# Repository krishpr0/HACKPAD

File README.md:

# The Weird MACROPAD

- A 4x4 Key MacroPad,

- So What's this,

This is a Large macropad, I wanted to develop this for the unusal uses such as while gaming, editing, and production of the 3d models shorcuts. 

This operates on the Seeed Studio Xiao RP2040 DIP module with the QMK firmware.

## Hardware:- 

- MCU: Seeed XIAO RP2040 DIP
- Switches: 16x Cherry MX compatible Switches
- LED: 16x SK6812 RBG LED

# Programming,
- Its running the default firmware (QMK firmware) but you can update it to the system you want.

# BOM,

- 16x Cherry MX Switches, 16x SK6812 MINI LEDs, 1x XIAO RP2040, 16x Blank DSA Keycaps,  4x M3x16 Bolts,  4x M3 Heatset Inserts ~100g PLA

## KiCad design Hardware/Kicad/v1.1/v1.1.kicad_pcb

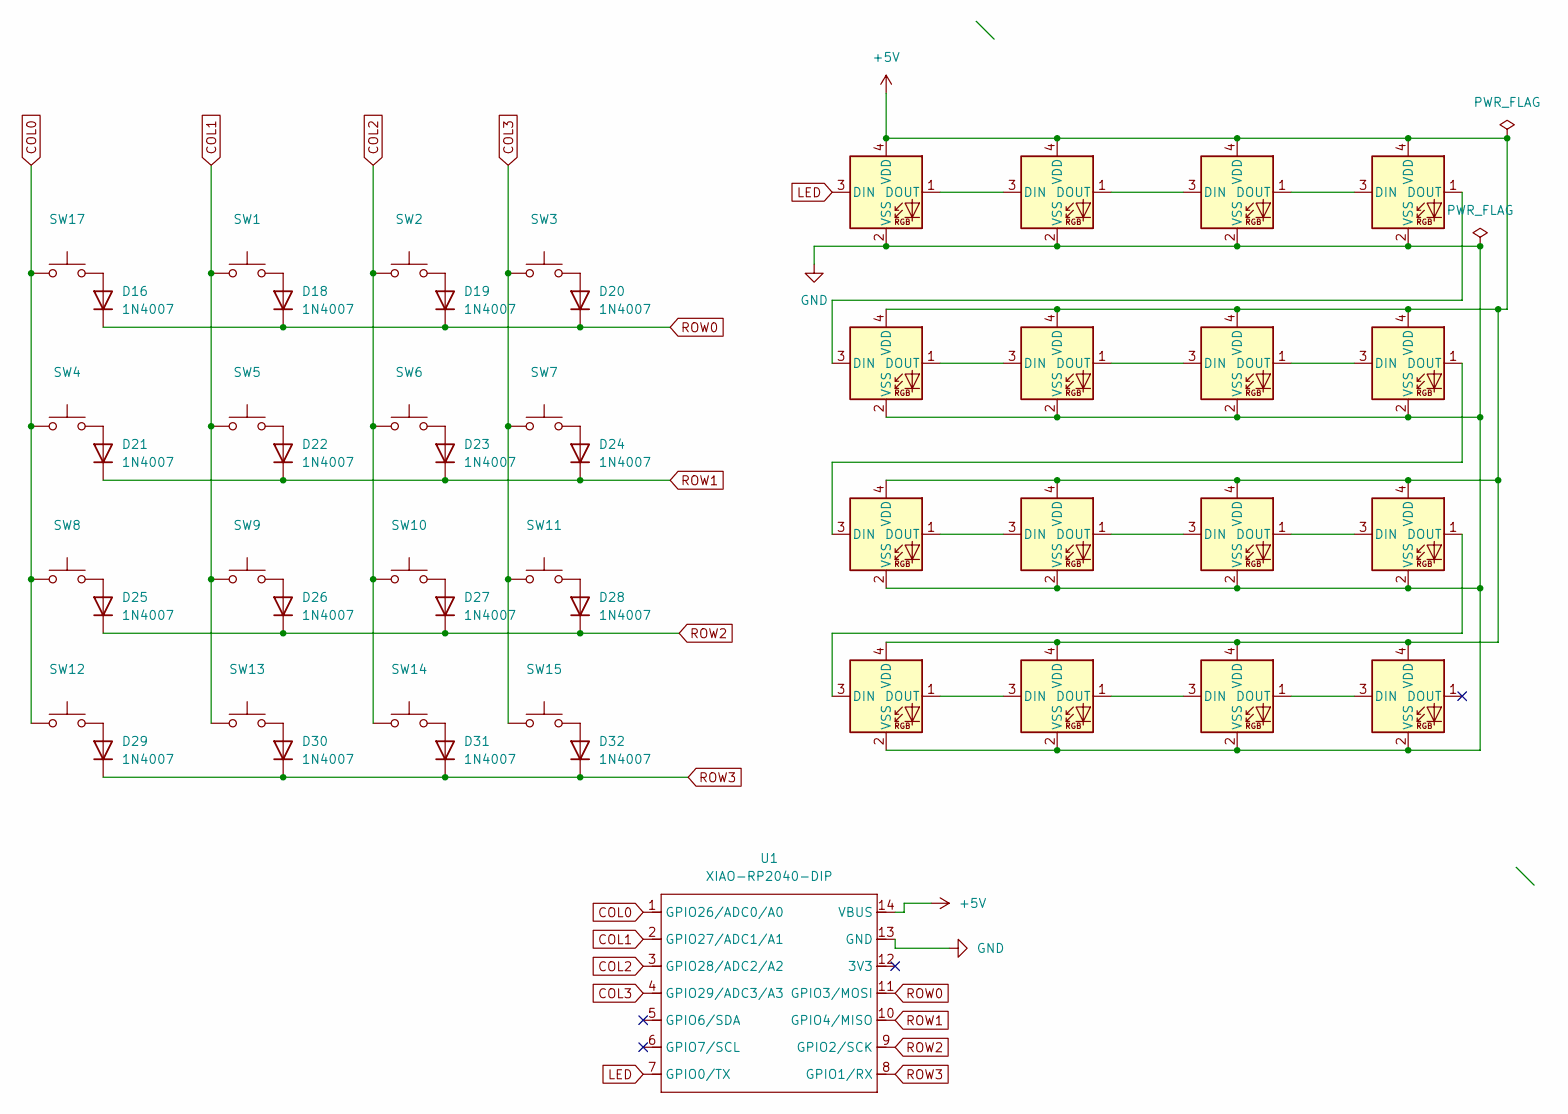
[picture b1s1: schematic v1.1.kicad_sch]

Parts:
D1, D2, D3, D4, D5, D6, D7, D8, D9, D10, D11, D12, D13, D14, D15, D17: SK6812MINI; LED_SK6812MINI_PLCC4_3.5x3.5mm_P1.75mm
D16, D18, D19, D20, D21, D22, D23, D24, D25, D26, D27, D28, D29, D30, D31, D32: 1N4007; D_DO-41_SOD81_P10.16mm_Horizontal
SW1, SW2, SW3, SW4, SW5, SW6, SW7, SW8, SW9, SW10, SW11, SW12, SW13, SW14, SW15, SW17: SW_Push; SW_Cherry_MX_1.00u_PCB
U1: XIAO-RP2040-DIP; XIAO-RP2040-SMD

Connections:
+5V: D1.4 (VDD), D2.4 (VDD), D3.4 (VDD), D4.4 (VDD), D5.4 (VDD), D6.4 (VDD), D7.4 (VDD), D8.4 (VDD), D9.4 (VDD), D10.4 (VDD), D11.4 (VDD), D12.4 (VDD), D13.4 (VDD), D14.4 (VDD), D15.4 (VDD), D17.4 (VDD), U1.14 (VBUS)
COL0: SW4.1, SW8.1, SW12.1, SW17.1, U1.1 (GPIO26/ADC0/A0)
COL1: SW1.1, SW5.1, SW9.1, SW13.1, U1.2 (GPIO27/ADC1/A1)
COL2: SW2.1, SW6.1, SW10.1, SW14.1, U1.3 (GPIO28/ADC2/A2)
COL3: SW3.1, SW7.1, SW11.1, SW15.1, U1.4 (GPIO29/ADC3/A3)
GND: D1.2 (VSS), D2.2 (VSS), D3.2 (VSS), D4.2 (VSS), D5.2 (VSS), D6.2 (VSS), D7.2 (VSS), D8.2 (VSS), D9.2 (VSS), D10.2 (VSS), D11.2 (VSS), D12.2 (VSS), D13.2 (VSS), D14.2 (VSS), D15.2 (VSS), D17.2 (VSS), U1.13 (GND)
LED: D17.3 (DIN), U1.7 (GPIO0/TX)
unnamed: D1.3 (DIN), D17.1 (DOUT)
unnamed: D1.1 (DOUT), D2.3 (DIN)
unnamed: D2.1 (DOUT), D3.3 (DIN)
unnamed: D3.1 (DOUT), D4.3 (DIN)
unnamed: D4.1 (DOUT), D5.3 (DIN)
unnamed: D5.1 (DOUT), D6.3 (DIN)
unnamed: D6.1 (DOUT), D7.3 (DIN)
unnamed: D7.1 (DOUT), D8.3 (DIN)
unnamed: D8.1 (DOUT), D9.3 (DIN)
unnamed: D9.1 (DOUT), D10.3 (DIN)
unnamed: D10.1 (DOUT), D11.3 (DIN)
unnamed: D11.1 (DOUT), D12.3 (DIN)
unnamed: D12.1 (DOUT), D13.3 (DIN)
unnamed: D13.1 (DOUT), D14.3 (DIN)
unnamed: D14.1 (DOUT), D15.3 (DIN)
unnamed: D16.2 (A), SW17.2
unnamed: D18.2 (A), SW1.2
unnamed: D19.2 (A), SW2.2
unnamed: D20.2 (A), SW3.2
unnamed: D21.2 (A), SW4.2
unnamed: D22.2 (A), SW5.2
unnamed: D23.2 (A), SW6.2
unnamed: D24.2 (A), SW7.2
unnamed: D25.2 (A), SW8.2
unnamed: D26.2 (A), SW9.2
unnamed: D27.2 (A), SW10.2
unnamed: D28.2 (A), SW11.2
unnamed: D29.2 (A), SW12.2
unnamed: D30.2 (A), SW13.2
unnamed: D31.2 (A), SW14.2
unnamed: D32.2 (A), SW15.2
ROW0: D16.1 (K), D18.1 (K), D19.1 (K), D20.1 (K), U1.11 (GPIO3/MOSI)
ROW1: D21.1 (K), D22.1 (K), D23.1 (K), D24.1 (K), U1.10 (GPIO4/MISO)
ROW2: D25.1 (K), D26.1 (K), D27.1 (K), D28.1 (K), U1.9 (GPIO2/SCK)
ROW3: D29.1 (K), D30.1 (K), D31.1 (K), D32.1 (K), U1.8 (GPIO1/RX)

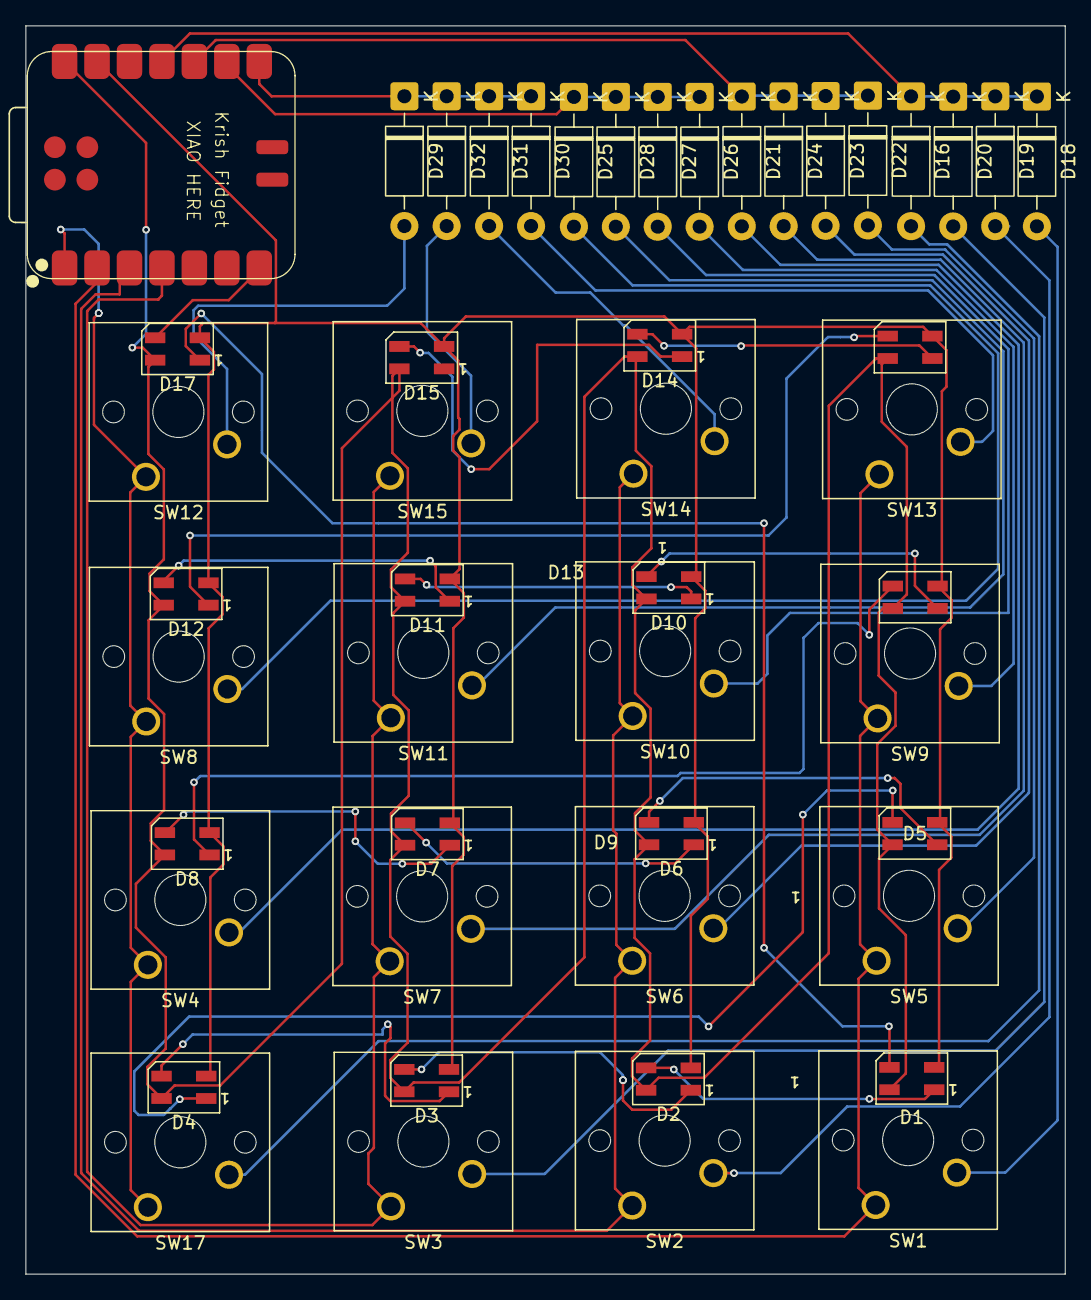
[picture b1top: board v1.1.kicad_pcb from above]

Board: 2 copper layers, 81.4 x 97.7 mm, 49 parts (0 on the bottom side), 42 nets.

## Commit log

2025-12-25 Initial commit - clean replacement
2025-12-25 Done I suppose
2025-12-27 Fixed the Readme files with organizing the PCB, Firmware, CAD into seperate Folder
